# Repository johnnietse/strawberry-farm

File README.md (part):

# G.O.S. - Greenhouse Operating System

**Wireless climate sensing and LED spectrum control for research strawberries in a phytotron.**

Sensor nodes measure temperature, humidity and light at the plants and send signed readings over
a Thread radio network to a Raspberry Pi. On the Pi, a strawberry canopy model works out what
the plants are doing, a trained controller picks a blue/red LED mix for each grow light, and the
answer goes back to each node, signed, in the reply to its next reading. Researchers watch and
annotate everything in a web dashboard; the data ends up in one ML-ready dataset.

**Status (2026-11-15):** both circuit boards are designed, simulated and ready to order; the
firmware builds; all software is tested end to end against a simulated node. Nothing has run on
real boards or plants yet. What is and is not verified: [Verification](#verification).
Review of how the parts fit together, and what to change next:
[`documentation/system_review.md`](documentation/system_review.md).

- [How it works](#how-it-works)
- [Hardware](#hardware)
- [Software and models](#software-and-models)
- [Run it](#run-it)
- [Dashboard, API, network](#dashboard-api-network)
- [Verification](#verification)
- [Repository map](#repository-map)

---

## How it works

```mermaid
graph LR
    subgraph Light["Light node (USB powered, Thread router)"]
        S1[SHT40 + TSL2591] --> M1[nRF52840<br/>Zephyr + OpenThread]
    end
    subgraph Climate["Climate node (battery, sleepy)"]
        S2[SHT40 + TSL2591] --> M2[nRF52840]
    end
    M1 -- "4-wire cable, 2 x PWM" --> L[LED driver board<br/>24 V, blue + red]
    M2 -. "Thread" .-> M1
    M1 -- "Thread: signed reading every 60 s" --> R[Raspberry Pi<br/>border router + Docker]
    M2 -. "Thread" .-> R
    R --> DB[(TimescaleDB)]
    DB --> BIO[biology engine<br/>canopy model + forecast]
    BIO --> CTL[LED controller<br/>PPO policy]
    CTL --> SP[setpoints]
    UI[dashboard] --> SP
    SP --> SAFE[safety monitor]
    SAFE -- "signed LED command in the reply" --> M1
```

*Figure 1. System overview. Each sensor node measures temperature, humidity and light and sends a signed reading over Thread to the Raspberry Pi. On the Pi the reading is stored, the biology engine works out the plant state, the LED controller turns it into an LED setpoint, and the safety monitor checks it before the signed LED command goes back to the light node, which drives its LED driver board over a 4-wire cable. Climate nodes only measure; their packets can reach the Pi through a light node.*

Two kinds of sensor node, same board, different firmware build:

*Table 1. The two node roles. Both use the same board; the firmware build decides whether a node is a USB-powered Thread router that drives an LED board, or a battery-powered sleepy device that only measures.*

| Node | Power | Thread role | Job |
|---|---|---|---|
| **Light node** | 5 V USB-C adapter | router: radio always on, relays for others | measures, and drives one LED driver board |
| **Climate node** | 18650 cell (months) | sleepy end device: wakes once a minute | measures only |

```mermaid
sequenceDiagram
    participant N as Node
    participant R as coap_receiver (Pi)
    participant DB as TimescaleDB
    participant B as biology engine
    participant C as LED controller
    loop every 60 s
        N->>R: CoAP POST, reading (HMAC-signed, counter)
        R->>R: check signature, EUI-64, counter
        R->>DB: store reading, read the node's LED setpoint
        R->>R: safety monitor: dark period, over 32 C, ramp limit
        R-->>N: 2.04 + LED command (signed, bound to this reading)
        N->>N: check tag and counter, set the PWM
    end
    loop every 60 s
        B->>DB: plant state: photosynthesis, transpiration, light integral, 2 h forecast
    end
    loop every 5 min
        C->>DB: LED setpoint per node (unless set by hand)
    end
```

*Figure 2. One control cycle. Every 60 s the node posts a signed reading; the receiver checks the signature, the node's identity and the counter, applies the safety rules to the node's LED setpoint and returns the LED command in the same CoAP reply, bound to that reading so it cannot be replayed. The biology engine (every 60 s) and the LED controller (every 5 min) update the plant state and the setpoints on their own schedules.*

If a node hears nothing for 15 minutes it switches its LEDs off; if the cable is unplugged the
LED board's pull-downs keep the LEDs off.

---

## Hardware

*Table 2. The hardware: what each piece contains and where its documentation is.*

| Piece | What it is | Docs |
|---|---|---|
| **Sensor node** rev 3.2, 40 x 65 mm, 4 layers | Raytac MDBT50Q (nRF52840) module; SHT40 temperature and humidity on a thermally isolated tongue; TSL2591 light; J6 input for a quantum (PAR) sensor; 18650 cell with BQ24074 USB-C charger, DW01A/FS8205A protection, reverse-cell FET; TPS62740 3.3 V buck; 4-pin LED cable connector | [`pcbs/gos_sensor_node/HARDWARE.md`](pcbs/gos_sensor_node/HARDWARE.md) |
| **LED driver** rev 1.1, 60 x 45 mm, 4 layers | two AL8860 constant-current channels, 333 mA or 667 mA (solder jumper per channel), 24 V input; blue 448 nm and red 655 nm strings of 4 LEDs; off when the control cable is unplugged | [`pcbs/led_driver/README.md`](pcbs/led_driver/README.md) |
| **Border router** | Raspberry Pi + Nordic nRF52840 Dongle (OpenThread border router); runs all the software in Docker | [`documentation/raspberry_pi_setup.md`](documentation/raspberry_pi_setup.md) |
| **Enclosures** | printed in ASA, generated from the KiCad boards and fit-checked | [`mechanical/README.md`](mechanical/README.md) |

| Sensor node | LED driver |
|---|---|
|  |  |
|  |  |
|  |  |

*Figure 3. The two boards, sensor node on the left and LED driver on the right. Row 1: 3D render of the assembled top side. Row 2: top copper layer. Row 3: the board in its printed enclosure with the lid raised.*

**Engineering drawings** of both enclosures (third-angle orthographic views with dimensions,
exploded isometric view with balloons, parts list, title block; generated by
[`mechanical/make_drawings.py`](mechanical/make_drawings.py)):

*Figure 4. Engineering drawing GOS-MECH-001, sensor node enclosure: top, front and right-side views with overall dimensions (85.0 x 130.0 x 48.0 mm; USB-C cut-out in the front wall, gland hole and vents in the right wall), exploded view with numbered balloons, parts list and title block.*

*Figure 5. Engineering drawing GOS-MECH-002, LED driver enclosure: 65.6 x 82.0 x 35.6 mm including the mounting flanges, control-cable slot and vents in the front wall, the two LED-plug openings in the right wall, exploded view, parts list and title block.*

**System assembly drawing** (GOS-MECH-003, two sheets): how the printed parts go together once
the boards and enclosures arrive. Sheet 1 shows the light node and the LED driver it drives at
the same true scale (1:2 when printed on A3), with one exploded view of both units, the control
cable between them and a combined parts list; its notes explain how to get the cable's plug
through the cable gland. Sheet 2 shows the installation in the growth chamber, every cable
(W1 to W7) in an interconnect list, the assembly sequence and the radio placement.

*Figure 6. System assembly drawing GOS-MECH-003, sheet 1: the light node and the LED driver at the same scale (1:2 on A3), one exploded view of both with the control cable (item 8), a combined parts list, and notes on routing the cable through the gland and the slot.*

*Figure 7. GOS-MECH-003, sheet 2: installation in the growth chamber (LED driver on the fixture frame, light node and climate nodes at canopy height, gateway outside), interconnect list W1 to W7 and R1, assembly sequence, and where to put the Thread Dongle.*

The **Raspberry Pi and the nRF52840 Dongle** are bought boards, so they get no printed
enclosure: the Pi goes in the official case for its model, and the Dongle sits outside it on a
short USB extension in a USB 2.0 port. USB 3.0 ports radiate noise in the 2.4 GHz band, and a
closed case or a metal chamber wall would shield the Dongle's antenna.

<details>
<summary>Schematics</summary>

Sensor node: [top level](docs/images/schematics/gos_sensor_node.svg) ·
[power](docs/images/schematics/gos_sensor_node-Power.svg) ·
[MCU](docs/images/schematics/gos_sensor_node-MCU.svg) ·
[sensors](docs/images/schematics/gos_sensor_node-Sensors.svg) ·
[connectors](docs/images/schematics/gos_sensor_node-Connectors.svg) ·
LED driver: [schematic](docs/images/schematics/led_driver.svg)

*Figure 8. Sensor node schematic, power sheet: the path from the USB-C input and the 18650 cell to the 3.3 V rail (charger with power path, cell protection, reverse-cell protection, buck converter).*

*Figure 9. LED driver schematic: 24 V input, two AL8860 constant-current channels (blue and red, 333 mA each), their PWM inputs from the 4-wire cable with pull-downs that keep the LEDs off when it is unplugged, and the LED-string connectors.*

</details>

**Firmware** (Zephyr, [`pcbs/gos_sensor_node/firmware`](pcbs/gos_sensor_node/firmware)):

*Table 3. Sensor node firmware builds: which build for which node, what to add to the build command, and the flash and RAM it uses (the nRF52840 has 1 MB and 256 KB).*

| Build | For | `west build -b raytac_mdbt50q_db_40/nrf52840 pcbs/gos_sensor_node/firmware ...` | Flash / RAM |
|---|---|---|---|
| bench | first power-on, with logging | (nothing more) | 214.6 / 62.4 KB |
| climate node | battery, in the phytotron | `-- -DEXTRA_CONF_FILE=low_power.conf` | 197.3 / 60.1 KB |
| climate node, locked | same, debugger blocked so keys cannot be read | `-- -DEXTRA_CONF_FILE="low_power.conf;lock.conf"` | 197.3 / 60.1 KB |
| light node | USB powered, Thread router | `-- -DEXTRA_CONF_FILE=router.conf` | 261.6 / 70.6 KB |

**Order and build:** [`documentation/ordering.md`](documentation/ordering.md) (JLCPCB settings,
every part with its stock, what to buy separately), then
[`documentation/bring_up.md`](documentation/bring_up.md) (first power-on, step by step).

**Revision 3.2** (2026-11-22) answers the three limits of rev 3.1 that `system_review.md`
listed: a 667 mA option on the LED driver (about twice the light, at most 240 umol m-2 s-1 per board),
a quantum (PAR) sensor input so the plant model gets photosynthetic light directly instead of an
estimate from lux, and a thermally isolated SHT40 (30 % less warming from the charger in a 2-D
estimate; readings taken while charging are still flagged). Before/after comparison, with every
test: [`documentation/rev3.2_changes.md`](documentation/rev3.2_changes.md). The rev 3.1 and
rev 1.0 boards are kept in [`pcbs/archive/`](pcbs/archive).

*Figure 10. Sensor node rev 3.1 against rev 3.2 with close-ups of the SHT40 corner: on rev 3.2 two notches and a slot (black) cut the sensor free on a tongue with no copper pour, and the PAR sensor header J6 sits beside J3.*

*Figure 11. LED driver rev 1.0 against rev 1.1: the second sense resistors with their solder jumpers (R5 / JP1, R6 / JP2) beside each AL8860, and the 10 uF capacitors (C6, C7) beside the inductors.*

---

## Software and models

All on the Raspberry Pi, in Docker Compose:

*Table 4. The Docker Compose services on the Raspberry Pi, what each does and where its code is.*

| Service | What it does | Code |
|---|---|---|
| `db` | TimescaleDB: readings, plant state, LED setpoints and commands, events, harvests | [`gateway/schema.sql`](gateway/schema.sql) |
| `coap_receiver` (profile `hardware`) | receives node readings over Thread, checks signatures and counters, stores them, replies with each node's signed LED command after the safety monitor | [`gateway/services/coap_receiver.py`](gateway/services/coap_receiver.py), [`led_safety.py`](gateway/services/led_safety.py) |
| `biology_engine` | canopy model on live data each minute, daily light integral, 2 h climate forecast | [`ml_engine/biology_engine.py`](ml_engine/biology_engine.py) |
| `ml_engine` | LED controller: PPO policy picks blue and red levels per node every 5 min | [`ml_engine/controller.py`](ml_engine/controller.py) |
| `sync_engine` | joins readings, LED commands, plant state, met data, events and harvests into one ML-ready CSV | [`gateway/services/sync.py`](gateway/services/sync.py) |
| `api` | REST API | [`gateway/services/api.py`](gateway/services/api.py) |
| `dashboard` | web dashboard on port 8080; also forwards `/api/` to the API | [`dashboard/`](dashboard) |
| `grafana` | time-series dashboard (temperature, humidity, VPD, photosynthesis, transpiration, light integral, LED levels, battery) on port 3000 | [`monitoring/`](monitoring) |
| `ollama` (profile `assistant`) | local language model for the research assistant, offline | [`gateway/services/assistant.py`](gateway/services/assistant.py) |
| `ingest`, `met_station` (profile `sim`) | simulated 40 nodes and met station, for a demo on a PC without hardware | `gateway/services/farm_sim.py`, `met_station.py` |
| `mqtt`, `mqtt_bridge` | MQTT input for other instruments (local only by default) | `gateway/services/mqtt_bridge.py` |

*Table 5. The models: the job each does, where its weights are, and the result of its check.*

| Job | Model | Weights | Result |
|---|---|---|---|
| What the plants are doing | strawberry canopy model: Farquhar photosynthesis, Medlyn stomata, Penman-Monteith transpiration | code | light-saturated photosynthesis 15.9 umol m-2 s-1, inside the 15 to 20 reported for strawberry |
| LED levels | PPO reinforcement-learning policy, trained in the canopy model, numpy on the Pi | [`ml_engine/models/led_policy.npz`](ml_engine/models) | within 0.5 % of a model-based optimiser on 60 held-out days |
| 2 h climate forecast | Chronos-Bolt Tiny (Amazon, Hugging Face), offline | [`ml_engine/models/hf/`](ml_engine/models/hf) | VPD error at 6 h 0.118 kPa, half of "no change" (0.245), on a year of measured weather |
| Notes to research events | Qwen2.5-1.5B-Instruct via Ollama, offline; Claude if a key is set; keyword rules otherwise | [GitHub release](https://github.com/johnnietse/strawberry-farm/releases/tag/models-2026-11-15) | 6 of 6 test notes filed correctly |

Model card with versions, licenses and checksums: [`ml_engine/models/README.md`](ml_engine/models/README.md).
Details and how to retrain: [`ml_engine/README.md`](ml_engine/README.md).

| Plant model | LED policy over one held-out day |
|---|---|
|  |  |
|  |  |

*Figure 12. Model checks. Top left: leaf photosynthesis against light at 15, 25 and 32 C, and against temperature; it saturates at 15.9 umol m-2 s-1, inside the 15 to 20 reported for strawberry, with an optimum at 28 C. Top right: one held-out day, daylight plus LED light at the canopy, and the LED levels the PPO policy chose (full through the photoperiod, off in the dark period). Bottom left: VPD forecast error against lead time over a year of measured weather; Chronos-Bolt Tiny has the lowest error, half that of "no change" at 6 h. Bottom right: daily reward of five LED strategies on 60 held-out days; PPO matches the model-based optimiser and beats fixed or no LED light.*

---

## Run it

**On a PC, without hardware** (simulated nodes):

```bash
git clone https://github.com/johnnietse/strawberry-farm.git
cd strawberry-farm
cp .env.example .env              # set POSTGRES_PASSWORD, GF_SECURITY_ADMIN_PASSWORD, GOS_API_TOKEN
                                  # (required: there are no default passwords; .env is never committed)
python -c "import secrets; print(secrets.token_hex(24))"     # a token for GOS_API_TOKEN
docker compose --profile sim up -d --build
```

Open http://localhost:8080, click **Access** at the top right and paste the token once.

**On the Raspberry Pi, with real nodes:** border router setup, then

```bash
docker compose --profile hardware --profile assistant up -d --build
OLLAMA="docker compose exec -T ollama ollama" bash ml_engine/models/fetch_models.sh
python gateway/tools/provision_node.py --index 1 --network-key <32 hex digits>   # per node
```

and flash each node with the build for its role (table above). Full guide:
[`documentation/raspberry_pi_setup.md`](documentation/raspberry_pi_setup.md), first power-on:
[`documentation/bring_up.md`](documentation/bring_up.md).

**Tests:**

```bash
cd gateway && python -m pytest tests && cd ..        # receiver, LED commands, safety, API, assistant
cd ml_engine && python -m pytest tests && cd ..      # canopy model, policy, controller
bash tests/e2e/run_e2e.sh                            # the whole loop in Docker, simulated node
```

---

## Dashboard, API, network

*Figure 13. The research dashboard during a run with the simulator. Top: latest reading per node. Middle: plant state from the biology engine and the LED level each node is set to. Bottom: set the LEDs by hand, log an event in plain words, and the LED commands actually sent after the safety monitor ("Asked" is the setpoint before it).*

The dashboard shows each node, the plant state and forecast, the LED level each node was sent
(with any safety note) and recent events; it sets LEDs by hand (timed, or until switched back)
and turns free-text notes into research events.

*Table 6. API endpoints. Reading is open; every POST and DELETE needs the API token.*

| Method | Endpoint | |
|---|---|---|
| GET | `/api/nodes`, `/api/plant`, `/api/led/commands`, `/api/events`, `/api/curated` | node readings, plant state with LED setpoint and forecast, LED commands sent, events, the ML dataset (CSV) |
| GET | `/api/phenotype/summary`, `/health` | last-hour summary, health |
| POST | `/api/led` | set LEDs by hand: `{"node": "RF-NODE-01" or "ALL", "blue_pct", "red_pct", "minutes"}` (`0` = until switched back) |
| DELETE | `/api/led/override` | back to automatic (`?node=` for one node) |
| POST | `/api/event`, `/api/yield`, `/api/assistant`, `/api/phenotype` | log an event or harvest; note to event; VPD and stress for given values |

Reading needs nothing; every change needs `Authorization: Bearer <GOS_API_TOKEN>` (from `.env`;
without it the API is read-only). The dashboard and the API share port 8080, so the system works
at whatever address the Pi has, on any network. The database, MQTT and port 5000 are reachable
from the Pi only. Other networks, other web sites, another server, HTTPS:
[`documentation/network_and_access.md`](documentation/network_and_access.md).

### Grafana

Grafana (port 3000, `monitoring/grafana/provisioning/dashboards/gos_phytotron.json`) is the
time-series view: ten panels per node, read straight from TimescaleDB. The screenshots below
are from the end-to-end test, for its test node `RF-NODE-07`, at the last hour.

*Figure 14. Grafana, test node RF-NODE-07, last hour: air temperature and relative humidity measured by the SHT40, VPD and canopy photosynthesis computed by the biology engine.*

**Air temperature and relative humidity**: the node's SHT40 readings. The test seeds 24 h of
history as a daily sine wave (temperature falling and humidity rising through this hour); the
last point, the jump to 22.3 C, is the first packet from the simulated node, signed and checked
like a real one. **VPD** (vapour pressure deficit) and **canopy photosynthesis** come from the
biology engine's canopy model (Farquhar-von Caemmerer-Berry with Medlyn stomata): about 0.85
kPa, comfortable for strawberries, and about 5 umol m-2 s-1 of net CO2 uptake at this light.

*Figure 15. Grafana: transpiration and daily light integral, computed by the biology engine.*

**Transpiration** (Penman-Monteith, about 45 g of water per m2 per hour) tells how fast the
plants use water. **Daily light integral** is the light summed since midnight; it is still
tiny here because the test started its light record minutes before the screenshot.

*Figure 16. Grafana: LED duty cycles sent to the node after the safety monitor, battery voltage and light at the node.*

**LED level sent, blue and red**: the duty cycle in the signed command the node received in its
reply, after the safety monitor (about 63 % blue and 78 % red here, set by the LED
controller). **Battery** and **light at the node** are flat because the test history uses a fixed
3,900 mV and 8,000 lux. The model panels and the LED panels show one point each: the biology
engine and the LED controller had run one cycle when the screenshot was taken; with the system
running they fill in every cycle, like the temperature panel.

---

## Verification

*Table 7. Verification so far. Each line was checked by a design tool, a simulation or a test; nothing has run on real boards yet.*

| Check | Result |
|---|---|
| KiCad DRC at every severity, with schematic parity | both boards: 0 violations, 0 unrouted |
| Layout review (USB pair, buck switching loop, antenna strip, LED switching loops) | measured; loops routed by hand ([`design_review.md`](documentation/design_review.md)) |
| LTspice: LED current and frequency, PWM dimming, CTRL fail-safe, battery sense, reversed cell | all pass after two fixes ([`simulation/README.md`](simulation/README.md)) |
| Datasheet checks: crystal load (nRF52840 LFXO table and Nordic's reference circuit), TSL2591 decoupling, FS8205A pinout | match ([`HARDWARE.md`](pcbs/gos_sensor_node/HARDWARE.md#not-verified)) |
| LTspice: crystal oscillator loop (frequency error, required gain, drive level) | +0.3 ppm at the design stray, at most 38 ppm over 0 to 4 pF |
| LTspice: LED driver rev 1.1, 667 mA option, 12 corners, PWM dimming | 672 to 675 mA, LEDs at most 680 mA (limit 700), inductor 0.775 A (rated 0.92 A), dimming proportional |
| Thermal model: SHT40 warming while charging, rev 3.1 against rev 3.2 | 11.7 K -> 8.2 K above the enclosure air (estimate) |
| Firmware: six builds (rev 3.2 adds two with the PAR sensor), devicetree with `dtc` | all build; no warnings from the project's code |
| Firmware host tests on a PC: LED-command check, and the PACKET_V5 builder against the gateway's format | both pass |
| Gateway tests | 88 pass |
| ML engine tests | 15 pass |
| End to end in Docker with the production images (torch, Chronos, Qwen): signed commands verified by the node, plant state and forecast, dashboard proxy, token refusals, manual override, assistant, ML dataset columns, Grafana; rev 3.2: PACKET_V5 with PAR stored | 17 of 17 checks pass (2026-11-24) |
| Enclosure fit (rev 3.2: PAR cable gland added) | 15 checks pass |

| LED channel at 24 V (LTspice) | PWM dimming 50 % (LTspice) |
|---|---|
|  |  |

*Figure 17. LTspice, LED driver. Left: current in one AL8860 channel at 24 V for the blue and red strings, switching at about 0.55 MHz with 104 mA ripple around the 333 mA target. Right: 50 % PWM dimming at 250 Hz; the LED current follows the CTRL signal and averages 168 mA, exactly half of full.*

*Figure 18. LTspice, sensor node 32.768 kHz crystal. Left: frequency error against board stray capacitance, +0.3 to +0.9 ppm at the 2 pF design value and at most 38 ppm over 0 to 4 pF, far inside the +/-500 ppm the radio needs. Middle: the loop's transimpedance peaks at 32 768.010 Hz, where it oscillates; this needs an oscillator gain of at least 1.24 uA/V. Right: the power dissipated in the crystal stays under its 0.5 uW limit up to 2 V peak to peak.*

*Figure 19. LTspice, LED driver rev 1.1: inductor current of one channel at 24 V with the jumper open (333 mA, grey) and bridged (667 mA, red). The ramp is the AL8860's hysteresis; at 667 mA it would peak above the deep red LED's 700 mA limit, which is why rev 1.1 also adds a 10 uF capacitor across each string: the LEDs (thick red line) stay between 668 and 680 mA.*

*Figure 20. Board temperature rise while charging (0.64 W in the charger), rev 3.1 against rev 3.2, from a 2-D thermal model. On rev 3.2 the SHT40 sits on a tongue cut free by two notches and a slot, so it warms 8.2 K instead of 11.7 K above the enclosure air; the rest of the board warms the same.*

**Not verified yet (needs hardware):** sleep current and battery life, Thread range, charging,
the LED current and light output, the plant-model parameters for your cultivar, the forecast on
phytotron air. Every issue found so far and its status:
[`documentation/issues_log.md`](documentation/issues_log.md).

---

## Repository map

*Table 8. Repository map: the top-level folders and what is in them.*

| Path | What |
|---|---|
| [`pcbs/gos_sensor_node/`](pcbs/gos_sensor_node) | sensor node: generators for schematic and board, routing, layout review, order files (`fab/`), drawings and renders (`docs/`), firmware |
| [`pcbs/led_driver/`](pcbs/led_driver) | LED driver board, same structure |
| [`mechanical/`](mechanical) | enclosures (OpenSCAD), fit check, engineering drawings, print files |
| [`simulation/`](simulation) | LTspice netlists, results, plots |
| [`gateway/`](gateway) | database schema, receiver, safety monitor, API, assistant, curation, simulators, node provisioning, tests |
| [`ml_engine/`](ml_engine) | canopy model, biology engine, lighting task, PPO training and policy, controller, forecasters, models, tests |
| [`dashboard/`](dashboard) | web dashboard and its nginx configuration |
| [`monitoring/`](monitoring) | Grafana datasource and dashboard, MQTT broker configuration |
| [`tests/e2e/`](tests/e2e) | end-to-end test |
| [`documentation/`](documentation) | guides and reviews (below) |
| `firmware/` | legacy rev 2 firmware, kept for reference; does not build for the current board |

*Table 9. The main documents and what each covers.*

| Document | |
|---|---|
| [`system_review.md`](documentation/system_review.md) | how the parts fit together, deployment plan |
| [`rev3.2_changes.md`](documentation/rev3.2_changes.md) | revision 3.2: the three board changes, before and after, with test results |
| [`design_review.md`](documentation/design_review.md) | electrical, firmware and mechanical review with evidence |
| [`issues_log.md`](documentation/issues_log.md) | every issue found, its effect and status |
| [`ordering.md`](documentation/ordering.md) | ordering both boards from JLCPCB, part stock, items bought separately |
| [`bring_up.md`](documentation/bring_up.md) | first power-on and bench tests |
| [`raspberry_pi_setup.md`](documentation/raspberry_pi_setup.md) | border router and the software stack |
| [`network_and_access.md`](documentation/network_and_access.md) | ports, token, other networks, sites and servers |
| [`hardware_protocol.md`](documentation/hardware_protocol.md) | reading packet and LED command formats |
| [`hardware_specs.md`](documentation/hardware_specs.md), [`nrf52840_pinout.md`](documentation/nrf52840_pinout.md) | board summary and pin map |
| [`requirements.md`](documentation/requirements.md) | course requirements checklist |

*Table 10. Course requirements: where the project meets each one, and its status.*

| Requirement | Where | Status |
|---|---|---|
| Wireless sensor network | sensor node rev 3.2, Thread mesh with router nodes | designed and simulated; not built |
| Database and data backbone | TimescaleDB, `sync.py` (readings, LED commands, plant state, met, events, harvests) | tested |
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
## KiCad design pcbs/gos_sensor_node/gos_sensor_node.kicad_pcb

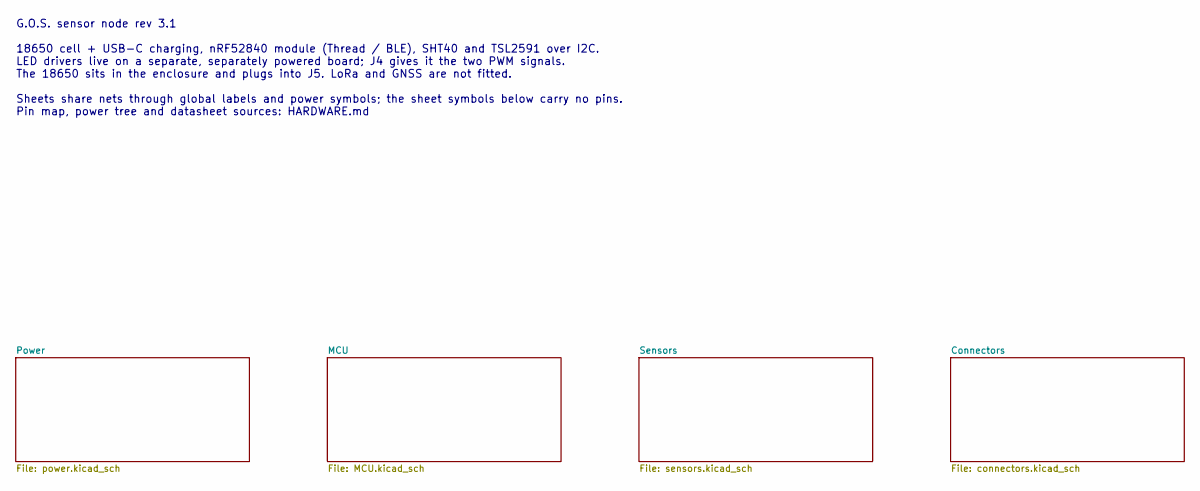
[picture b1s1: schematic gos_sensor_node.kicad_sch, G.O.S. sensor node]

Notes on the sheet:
G.O.S. sensor node rev 3.1 18650 cell + USB-C charging, nRF52840 module (Thread / BLE), SHT40 and TSL2591 over I2C. LED drivers live on a separate, separately powered board; J4 gives it the two PWM signals. The 18650 sits in the enclosure and plugs into J5. LoRa and GNSS are not fitted. Sheets shar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

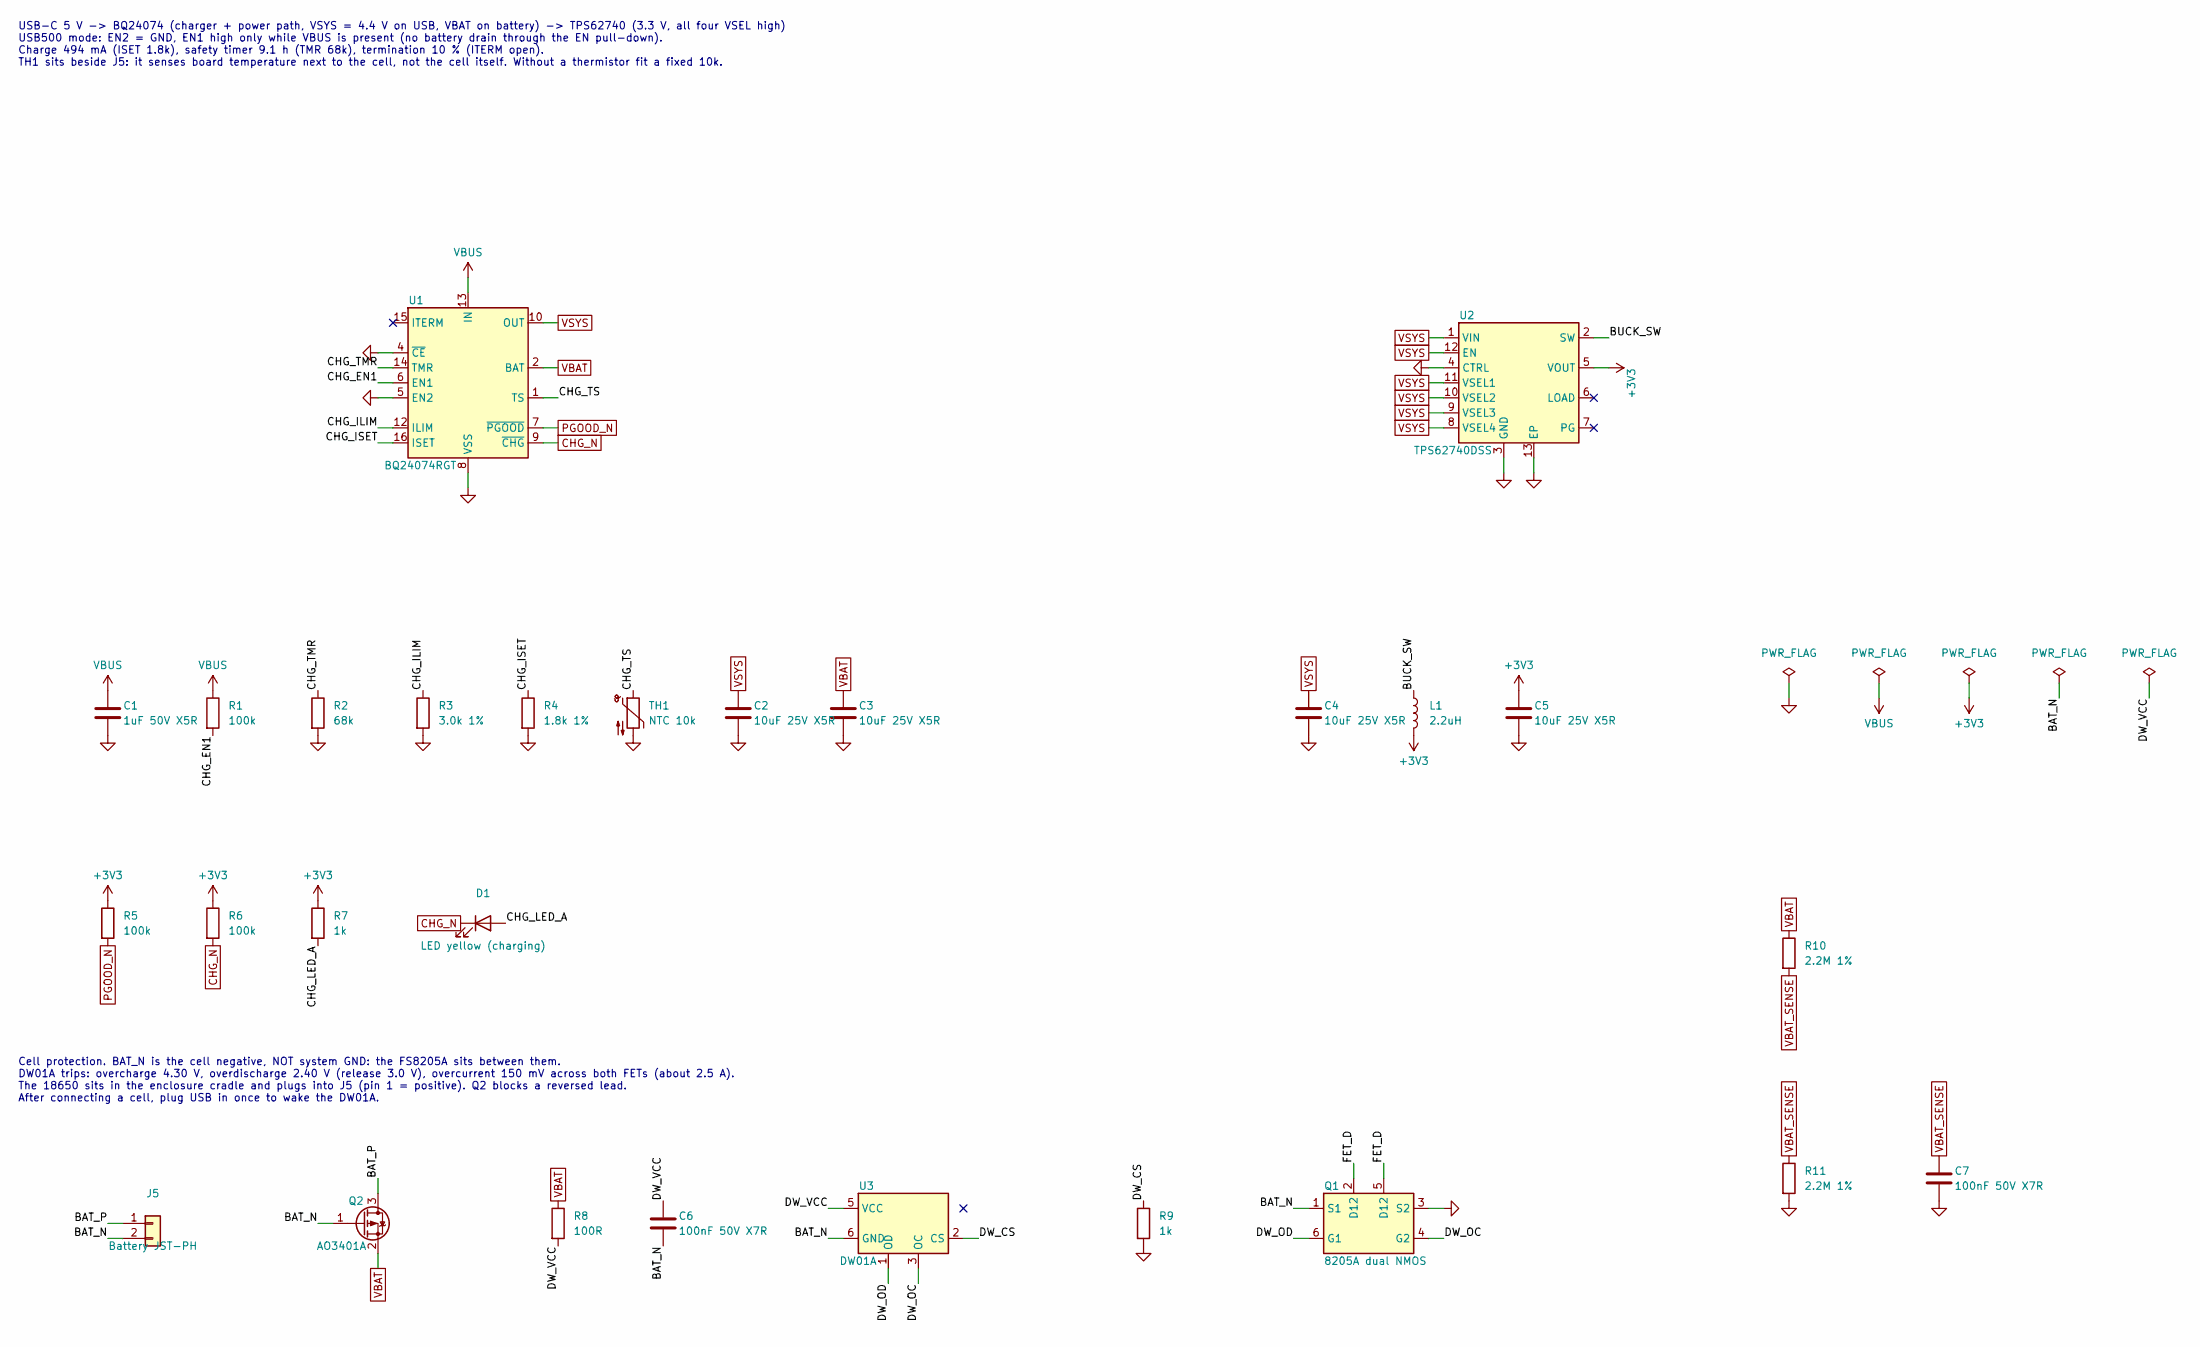
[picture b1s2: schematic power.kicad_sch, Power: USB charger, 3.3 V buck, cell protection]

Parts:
C1: 1uF 50V X5R; C_0603_1608Metric; MPN CL10A105KB8NNNC; LCSC C15849
C2, C3, C4, C5: 10uF 25V X5R; C_0805_2012Metric; MPN CL21A106KAYNNNE; LCSC C15850
C6, C7: 100nF 50V X7R; C_0603_1608Metric; MPN CC0603KRX7R9BB104; LCSC C14663
D1: LED yellow (charging); LED_0603_1608Metric; MPN KT-0603Y; LCSC C2287
J5: Battery JST-PH; JST_PH_S2B-PH-K_1x02_P2.00mm_Horizontal; MPN S2B-PH-K-S; LCSC C173752
L1: 2.2uH; L_APV_ANR3015; MPN SWPA3015S2R2MT; LCSC C43389
Q1: 8205A dual NMOS; SOT-23-6; MPN FS8205A; LCSC C908265
Q2: AO3401A; SOT-23; MPN AO3401A; LCSC C15127
R1, R5, R6: 100k; R_0603_1608Metric; MPN 0603WAF1003T5E; LCSC C25803
R2: 68k; R_0603_1608Metric; MPN 0603WAF6802T5E; LCSC C23231
R3: 3.0k 1%; R_0603_1608Metric; MPN 0603WAF3001T5E; LCSC C4211
R4: 1.8k 1%; R_0603_1608Metric; MPN 0603WAF1801T5E; LCSC C4177
R7, R9: 1k; R_0603_1608Metric; MPN 0603WAF1001T5E; LCSC C21190
R8: 100R; R_0603_1608Metric; MPN 0603WAF1000T5E; LCSC C22775
R10, R11: 2.2M 1%; R_0603_1608Metric; MPN 0603WAF2204T5E; LCSC C22938
TH1: NTC 10k; R_0603_1608Metric; MPN NCP18XH103F03RB; LCSC C13564
U1: BQ24074RGT; VQFN-16-1EP_3x3mm_P0.5mm_EP1.6x1.6mm; MPN BQ24074RGTR; LCSC C54313
U2: TPS62740DSS; WSON-12-1EP_3x2mm_P0.5mm_EP1x2.65; MPN TPS62740DSSR; LCSC C128606
U3: DW01A; SOT-23-6; MPN DW01A; LCSC C351410

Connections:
+3V3: C5.1, L1.2, R5.1, R6.1, R7.1, U2.5 (VOUT); also elsewhere on the board
/Power/BAT_N: C6.2, J5.2, Q1.1 (S1), Q2.1 (G), U3.6 (GND)
/Power/BAT_P: J5.1, Q2.3 (D)
/Power/BUCK_SW: L1.1, U2.2 (SW)
/Power/CHG_EN1: R1.2, U1.6 (EN1)
/Power/CHG_ILIM: R3.1, U1.12 (ILIM)
/Power/CHG_ISET: R4.1, U1.16 (ISET)
/Power/CHG_LED_A: D1.2 (A), R7.2
/Power/CHG_TMR: R2.1, U1.14 (TMR)
/Power/CHG_TS: TH1.1, U1.1 (TS)
/Power/DW_CS: R9.1, U3.2 (CS)
/Power/DW_OC: Q1.4 (G2), U3.3 (OC)
/Power/DW_OD: Q1.6 (G1), U3.1 (OD)
/Power/DW_VCC: C6.1, R8.2, U3.5 (VCC)
/Power/FET_D: Q1.2 (D12), Q1.5 (D12)
CHG_N: D1.1 (K), R6.2, U1.9 (~CHG); also elsewhere on the board
GND: C1.2, C2.2, C3.2, C4.2, C5.2, C7.2, Q1.3 (S2), R2.2, R3.2, R4.2, R9.2, R11.2, TH1.2, U1.4 (~CE), U1.5 (EN2), U1.8 (VSS), U1.17 (VSS), U2.3 (GND), U2.4 (CTRL), U2.13 (EP); also elsewhere on the board
PGOOD_N: R5.2, U1.7 (~PGOOD); also elsewhere on the board
VBAT: C3.1, Q2.2 (S), R8.1, R10.1, U1.2 (BAT), U1.3 (BAT); also elsewhere on the board
VBAT_SENSE: C7.1, R10.2, R11.1; also elsewhere on the board
VBUS: C1.1, R1.1, U1.13 (IN); also elsewhere on the board
VSYS: C2.1, C4.1, U1.10 (OUT), U1.11 (OUT), U2.1 (VIN), U2.8 (VSEL4), U2.9 (VSEL3), U2.10 (VSEL2), U2.11 (VSEL1), U2.12 (EN); also elsewhere on the board

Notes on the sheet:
USB-C 5 V -> BQ24074 (charger + power path, VSYS = 4.4 V on USB, VBAT on battery) -> TPS62740 (3.3 V, all four VSEL high) USB500 mode: EN2 = GND, EN1 high only while VBUS is present (no battery drain through the EN pull-down). Charge 494 mA (ISET 1.8k), safety timer 9.1 h (TMR 68k), termination 10 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
Cell protection. BAT_N is the cell negative, NOT system GND: the FS8205A sits between them. DW01A trips: overcharge 4.30 V, overdischarge 2.40 V (release 3.0 V), overcurrent 150 mV across both FETs (about 2.5 A). The 18650 sits in the enclosure cradle and plugs into J5 (pin 1 = positive). Q2 blocks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

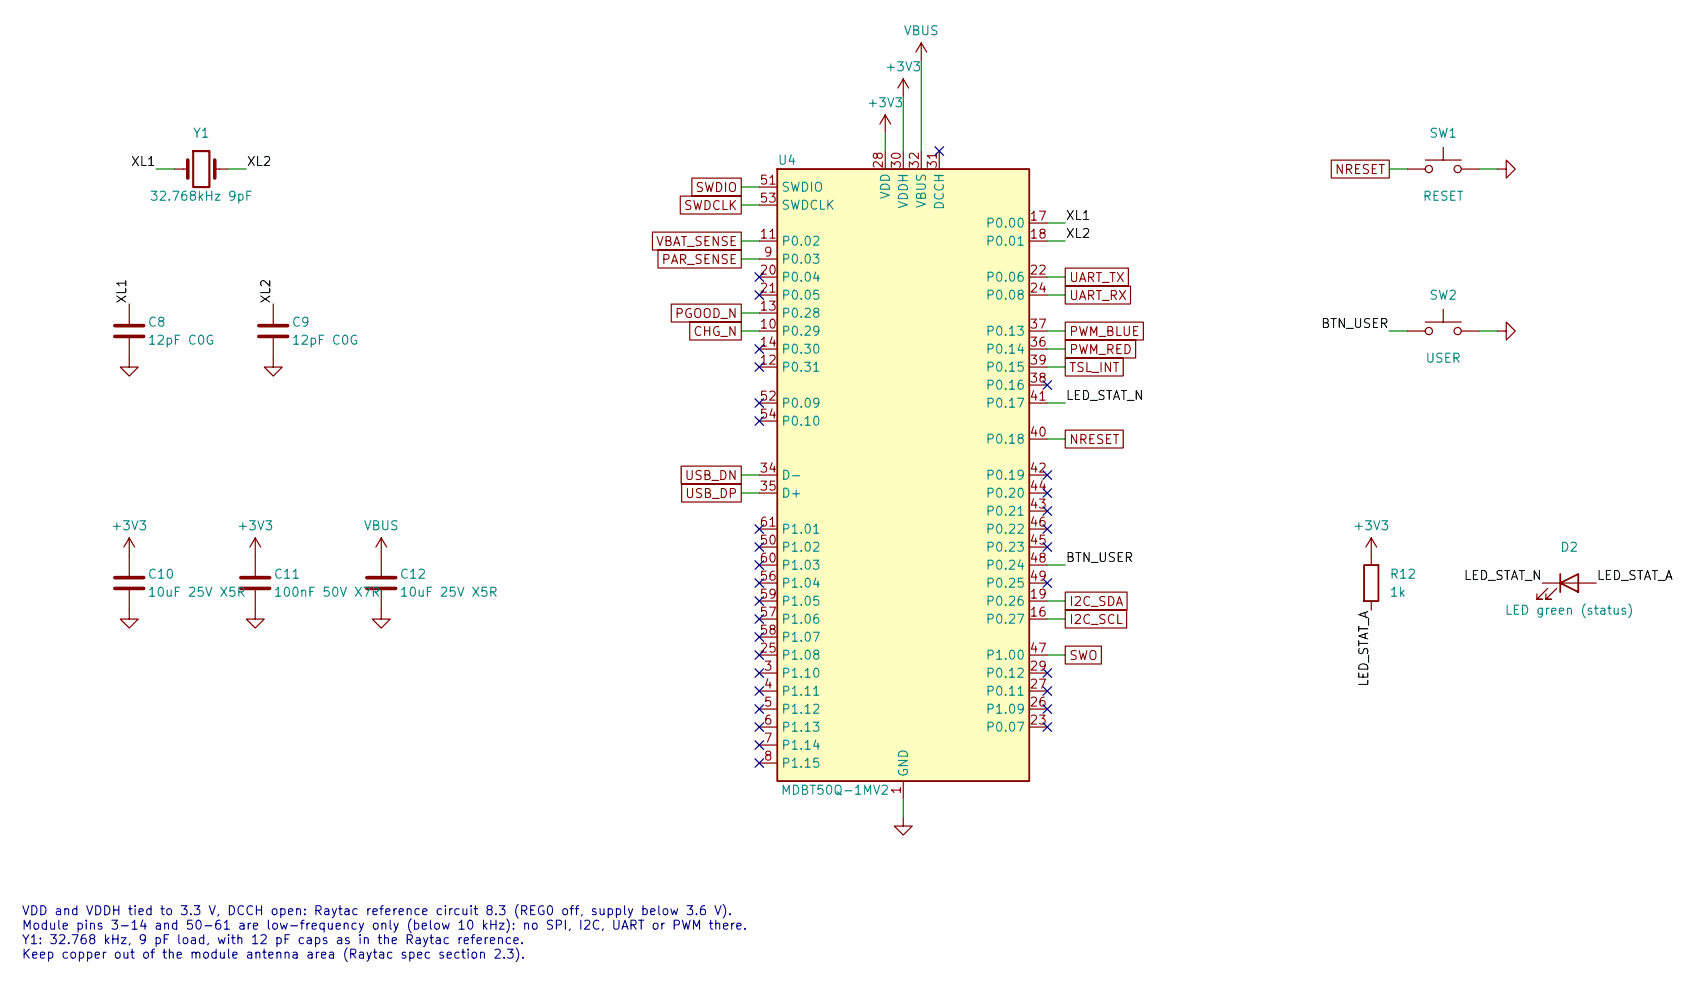
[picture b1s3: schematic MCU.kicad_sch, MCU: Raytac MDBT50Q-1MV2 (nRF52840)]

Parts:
C8, C9: 12pF C0G; C_0603_1608Metric; MPN CL10C120JB8NNNC; LCSC C38523
C10, C12: 10uF 25V X5R; C_0805_2012Metric; MPN CL21A106KAYNNNE; LCSC C15850
C11: 100nF 50V X7R; C_0603_1608Metric; MPN CC0603KRX7R9BB104; LCSC C14663
D2: LED green (status); LED_0603_1608Metric; MPN KT-0603G; LCSC C12624
R12: 1k; R_0603_1608Metric; MPN 0603WAF1001T5E; LCSC C21190
SW1: RESET; SW_SPST_B3U-1000P; MPN B3U-1000P; LCSC C231329
SW2: USER; SW_SPST_B3U-1000P; MPN B3U-1000P; LCSC C231329
U4: MDBT50Q-1MV2; Raytac_MDBT50Q; MPN MDBT50Q-1MV2; LCSC C5118826
Y1: 32.768kHz 9pF; Crystal_SMD_3215-2Pin_3.2x1.5mm; MPN ABS07-32.768KHZ-9-T; LCSC C179635

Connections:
+3V3: C10.1, C11.1, R12.1, U4.28 (VDD), U4.30 (VDDH); also elsewhere on the board
/MCU/BTN_USER: SW2.1, U4.48 (P0.24)
/MCU/LED_STAT_A: D2.2 (A), R12.2
/MCU/LED_STAT_N: D2.1 (K), U4.41 (P0.17)
/MCU/XL1: C8.1, U4.17 (P0.00), Y1.1
/MCU/XL2: C9.1, U4.18 (P0.01), Y1.2
CHG_N: U4.10 (P0.29); also elsewhere on the board
GND: C8.2, C9.2, C10.2, C11.2, C12.2, SW1.2, SW2.2, U4.1 (GND), U4.2 (GND), U4.15 (GND), U4.33 (GND), U4.55 (GND); also elsewhere on the board
I2C_SCL: U4.16 (P0.27); also elsewhere on the board
I2C_SDA: U4.19 (P0.26); also elsewhere on the board
NRESET: SW1.1, U4.40 (P0.18); also elsewhere on the board
PAR_SENSE: U4.9 (P0.03); also elsewhere on the board
PGOOD_N: U4.13 (P0.28); also elsewhere on the board
PWM_BLUE: U4.37 (P0.13); also elsewhere on the board
PWM_RED: U4.36 (P0.14); also elsewhere on the board
SWDCLK: U4.53 (SWDCLK); also elsewhere on the board
SWDIO: U4.51 (SWDIO); also elsewhere on the board
SWO: U4.47 (P1.00); also elsewhere on the board
TSL_INT: U4.39 (P0.15); also elsewhere on the board
UART_RX: U4.24 (P0.08); also elsewhere on the board
UART_TX: U4.22 (P0.06); also elsewhere on the board
USB_DN: U4.34 (D-); also elsewhere on the board
USB_DP: U4.35 (D+); also elsewhere on the board
VBAT_SENSE: U4.11 (P0.02); also elsewhere on the board
VBUS: C12.1, U4.32 (VBUS); also elsewhere on the board

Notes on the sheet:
VDD and VDDH tied to 3.3 V, DCCH open: Raytac reference circuit 8.3 (REG0 off, supply below 3.6 V). Module pins 3-14 and 50-61 are low-frequency only (below 10 kHz): no SPI, I2C, UART or PWM there. Y1: 32.768 kHz, 9 pF load, with 12 pF caps as in the Raytac reference. Keep copper out of the module 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

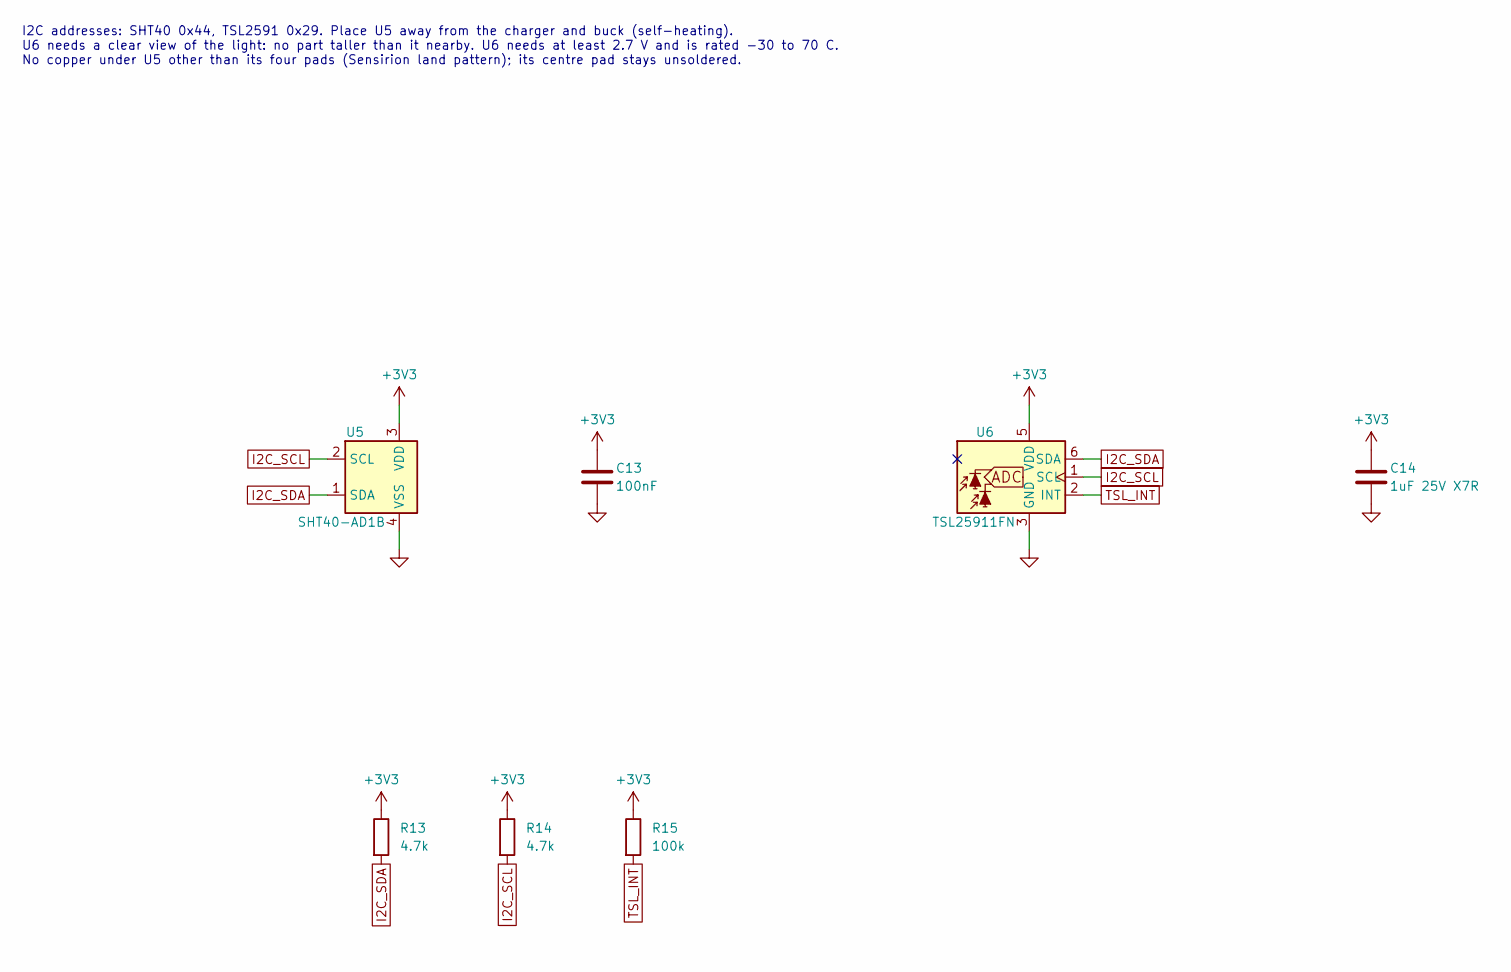
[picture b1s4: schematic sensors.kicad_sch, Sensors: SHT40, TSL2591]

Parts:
C13: 100nF; C_0603_1608Metric
C14: 1uF 25V X7R; C_0603_1608Metric
R13, R14: 4.7k; R_0603_1608Metric
R15: 100k; R_0603_1608Metric
U5: SHT40-AD1B; Sensirion_DFN-4_1.5x1.5mm_P0.8mm_SHT4x_NoCentralPad; MPN SHT40-AD1B-R2
U6: TSL25911FN; AMS_TSL25911FN; MPN TSL25911FN

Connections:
+3V3: C13.1, C14.1, R13.1, R14.1, R15.1, U5.3 (VDD), U6.5 (VDD); also elsewhere on the board
GND: C13.2, C14.2, U5.4 (VSS), U6.3 (GND); also elsewhere on the board
I2C_SCL: R14.2, U5.2 (SCL), U6.1 (SCL); also elsewhere on the board
I2C_SDA: R13.2, U5.1 (SDA), U6.6 (SDA); also elsewhere on the board
TSL_INT: R15.2, U6.2 (INT); also elsewhere on the board

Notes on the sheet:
I2C addresses: SHT40 0x44, TSL2591 0x29. Place U5 away from the charger and buck (self-heating). U6 needs a clear view of the light: no part taller than it nearby. U6 needs at least 2.7 V and is rated -30 to 70 C. No copper under U5 other than its four pads (Sensirion land pattern); its centre pad 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

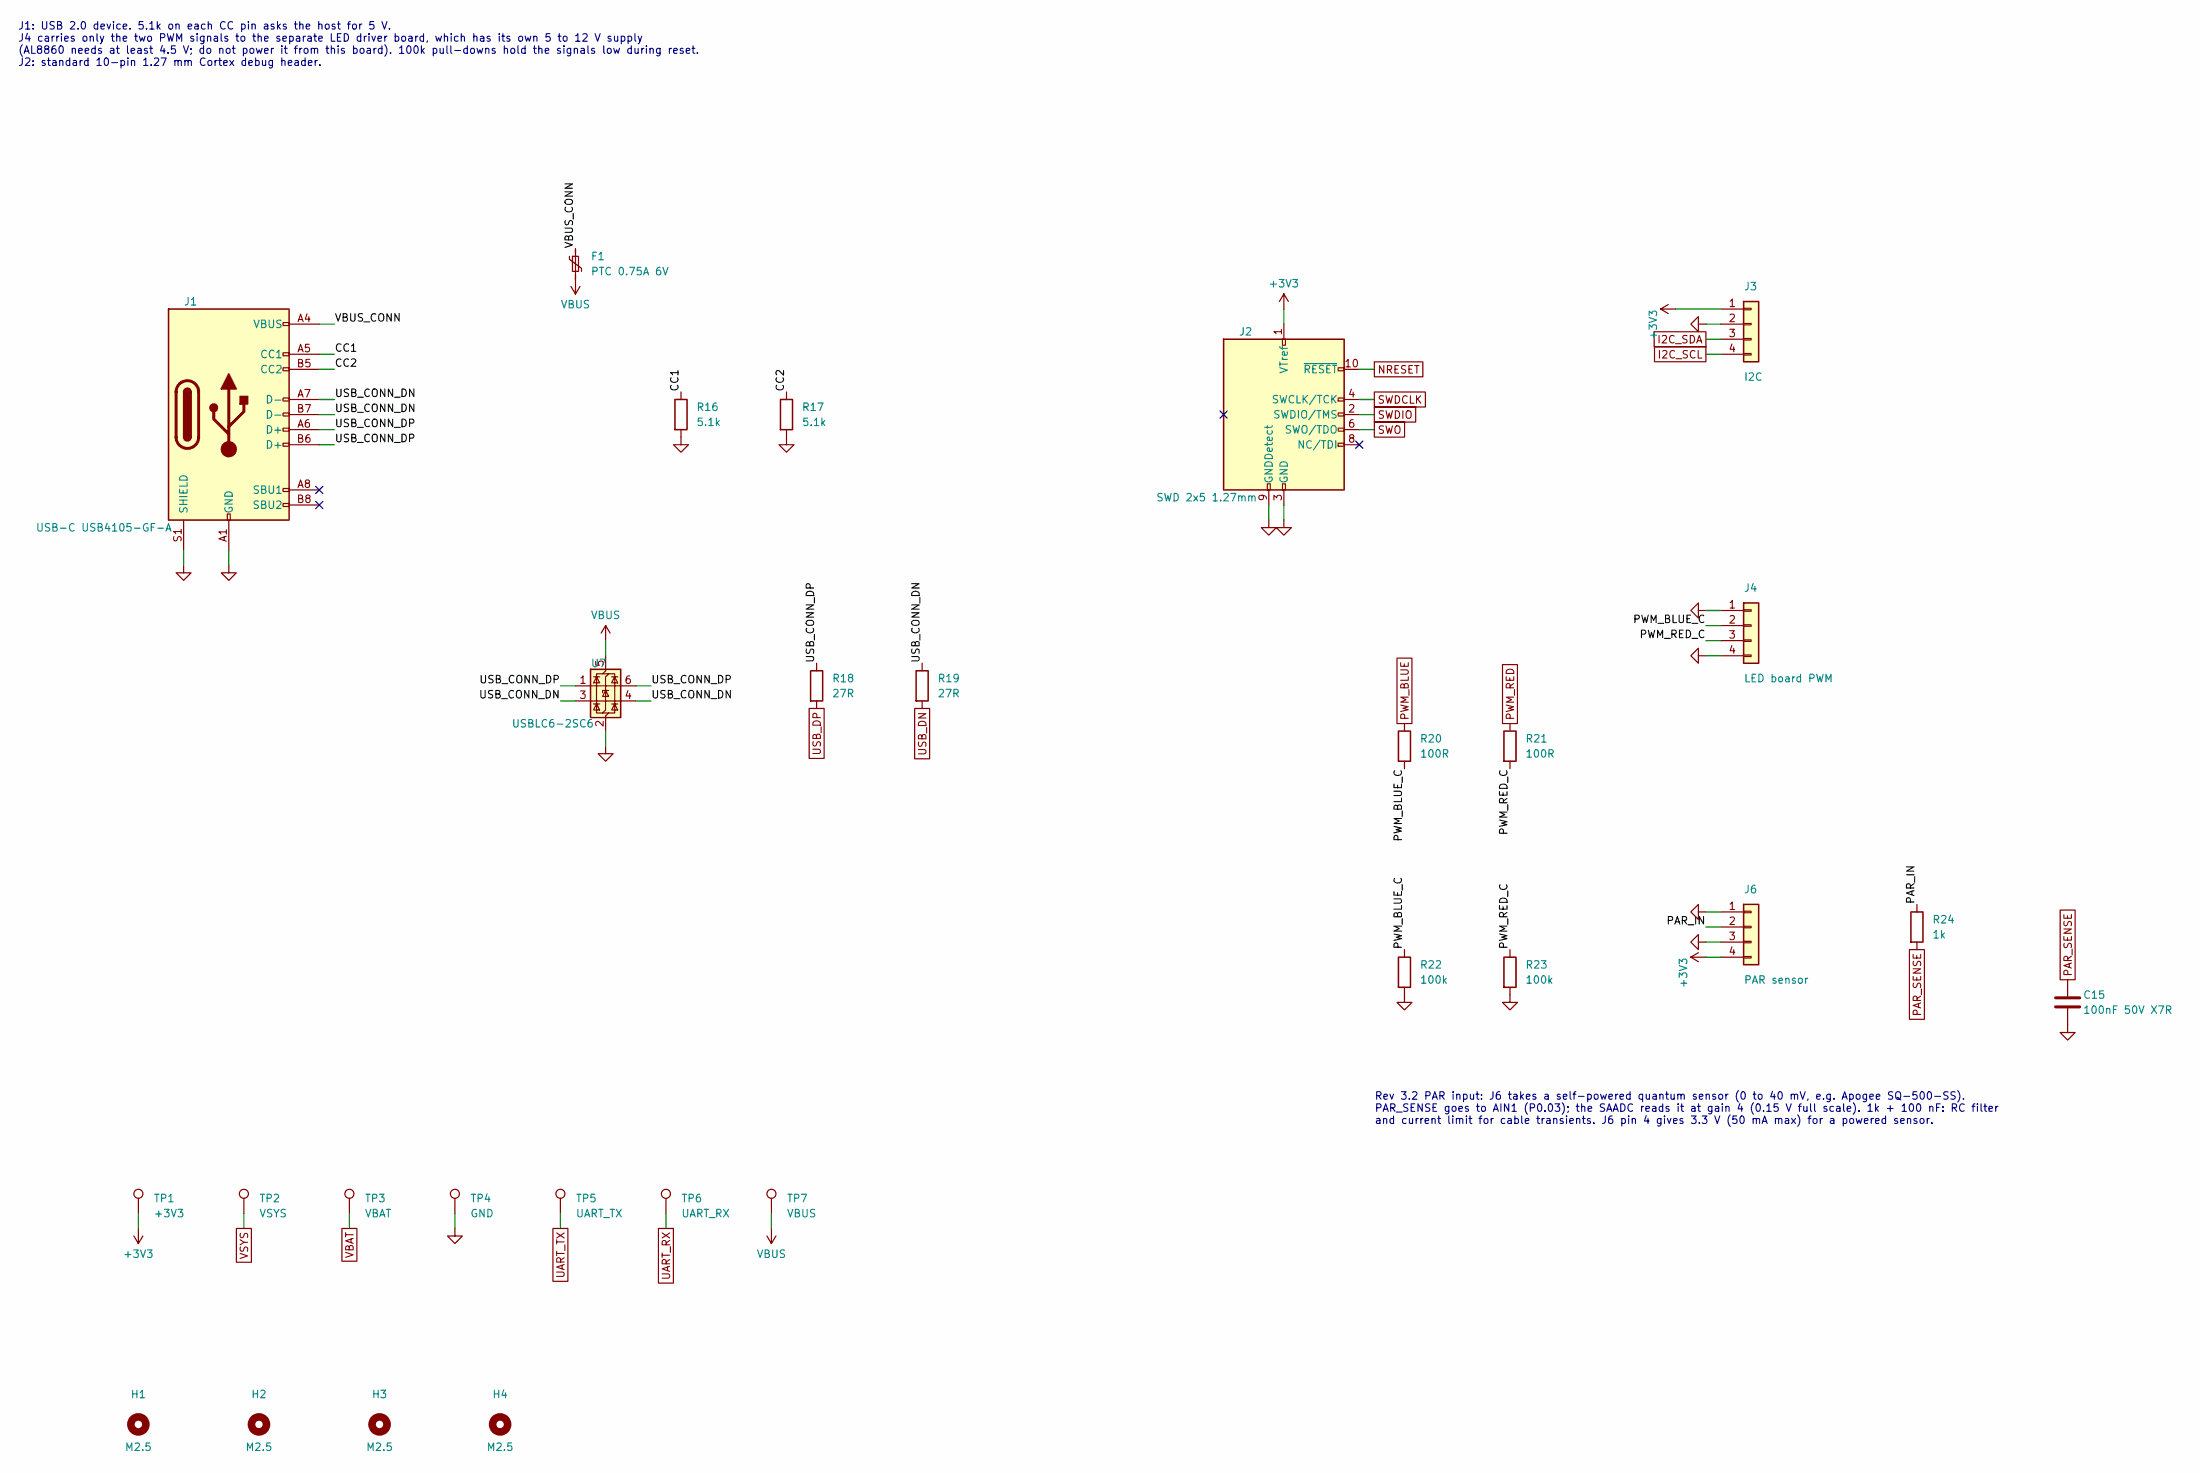
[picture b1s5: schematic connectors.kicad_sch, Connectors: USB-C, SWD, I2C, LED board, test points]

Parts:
C15: 100nF 50V X7R; C_0603_1608Metric; MPN CC0603KRX7R9BB104; LCSC C14663
F1: PTC 0.75A 6V; Fuse_1206_3216Metric; MPN SMD1206P075TF; LCSC C20987
H1, H2, H3, H4: M2.5; MountingHole_2.7mm_M2.5
J1: USB-C USB4105-GF-A; USB_C_Receptacle_GCT_USB4105-xx-A_16P_TopMnt_Horizontal; MPN USB4105-GF-A; LCSC C3020560
J2: SWD 2x5 1.27mm; PinHeader_2x05_P1.27mm_Vertical_SMD; MPN FTSH-105-01-L-DV-K; LCSC C5155080
J3: I2C; PinHeader_1x04_P2.54mm_Vertical; MPN 254PZ-1x4P-V; LCSC C53055674
J4: LED board PWM; PinHeader_1x04_P2.54mm_Vertical; MPN 254PZ-1x4P-V; LCSC C53055674
J6: PAR sensor; PinHeader_1x04_P2.54mm_Vertical; MPN 254PZ-1x4P-V; LCSC C53055674
R16, R17: 5.1k; R_0603_1608Metric; MPN 0603WAF5101T5E; LCSC C23186
R18, R19: 27R; R_0603_1608Metric; MPN 0603WAF270JT5E; LCSC C25190
R20, R21: 100R; R_0603_1608Metric; MPN 0603WAF1000T5E; LCSC C22775
R22, R23: 100k; R_0603_1608Metric; MPN 0603WAF1003T5E; LCSC C25803
R24: 1k; R_0603_1608Metric; MPN 0603WAF1001T5E; LCSC C21190
TP1: +3V3; TestPoint_Pad_D1.0mm
TP2: VSYS; TestPoint_Pad_D1.0mm
TP3: VBAT; TestPoint_Pad_D1.0mm
TP4: GND; TestPoint_Pad_D1.0mm
TP5: UART_TX; TestPoint_Pad_D1.0mm
TP6: UART_RX; TestPoint_Pad_D1.0mm
TP7: VBUS; TestPoint_Pad_D1.0mm
U7: USBLC6-2SC6; SOT-23-6; MPN USBLC6-2SC6; LCSC C7519

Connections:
+3V3: J2.1 (VTref), J3.1, J6.4, TP1.1; also elsewhere on the board
/Connectors/CC1: J1.A5 (CC1), R16.1
/Connectors/CC2: J1.B5 (CC2), R17.1
/Connectors/PAR_IN: J6.2, R24.1
/Connectors/PWM_BLUE_C: J4.2, R20.2, R22.1
/Connectors/PWM_RED_C: J4.3, R21.2, R23.1
/Connectors/USB_CONN_DN: J1.A7 (D-), J1.B7 (D-), R19.1, U7.3 (I/O2), U7.4 (I/O2)
/Connectors/USB_CONN_DP: J1.A6 (D+), J1.B6 (D+), R18.1, U7.1 (I/O1), U7.6 (I/O1)
/Connectors/VBUS_CONN: F1.1, J1.A4 (VBUS), J1.A9 (VBUS), J1.B4 (VBUS), J1.B9 (VBUS)
GND: C15.2, J1.A1 (GND), J1.A12 (GND), J1.B1 (GND), J1.B12 (GND), J1.S1 (SHIELD), J2.3 (GND), J2.5 (GND), J2.9 (GNDDetect), J3.2, J4.1, J4.4, J6.1, J6.3, R16.2, R17.2, R22.2, R23.2, TP4.1, U7.2 (GND); also elsewhere on the board
I2C_SCL: J3.4; also elsewhere on the board
I2C_SDA: J3.3; also elsewhere on the board
NRESET: J2.10 (~RESET); also elsewhere on the board
PAR_SENSE: C15.1, R24.2; also elsewhere on the board
PWM_BLUE: R20.1; also elsewhere on the board
PWM_RED: R21.1; also elsewhere on the board
SWDCLK: J2.4 (SWCLK/TCK); also elsewhere on the board
SWDIO: J2.2 (SWDIO/TMS); also elsewhere on the board
SWO: J2.6 (SWO/TDO); also elsewhere on the board
UART_RX: TP6.1; also elsewhere on the board
UART_TX: TP5.1; also elsewhere on the board
USB_DN: R19.2; also elsewhere on the board
USB_DP: R18.2; also elsewhere on the board
VBAT: TP3.1; also elsewhere on the board
VBUS: F1.2, TP7.1, U7.5 (VBUS); also elsewhere on the board
VSYS: TP2.1; also elsewhere on the board

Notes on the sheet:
J1: USB 2.0 device. 5.1k on each CC pin asks the host for 5 V. J4 carries only the two PWM signals to the separate LED driver board, which has its own 5 to 12 V supply (AL8860 needs at least 4.5 V; do not power it from this board). 100k pull-downs hold the signals low during reset. J2: standard 10-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
Rev 3.2 PAR input: J6 takes a self-powered quantum sensor (0 to 40 mV, e.g. Apogee SQ-500-SS). PAR_SENSE goes to AIN1 (P0.03); the SAADC reads it at gain 4 (0.15 V full scale). 1k + 100 nF: RC filter and current limit for cable transients. J6 pin 4 gives 3.3 V (50 mA max) for a powered sensor.
